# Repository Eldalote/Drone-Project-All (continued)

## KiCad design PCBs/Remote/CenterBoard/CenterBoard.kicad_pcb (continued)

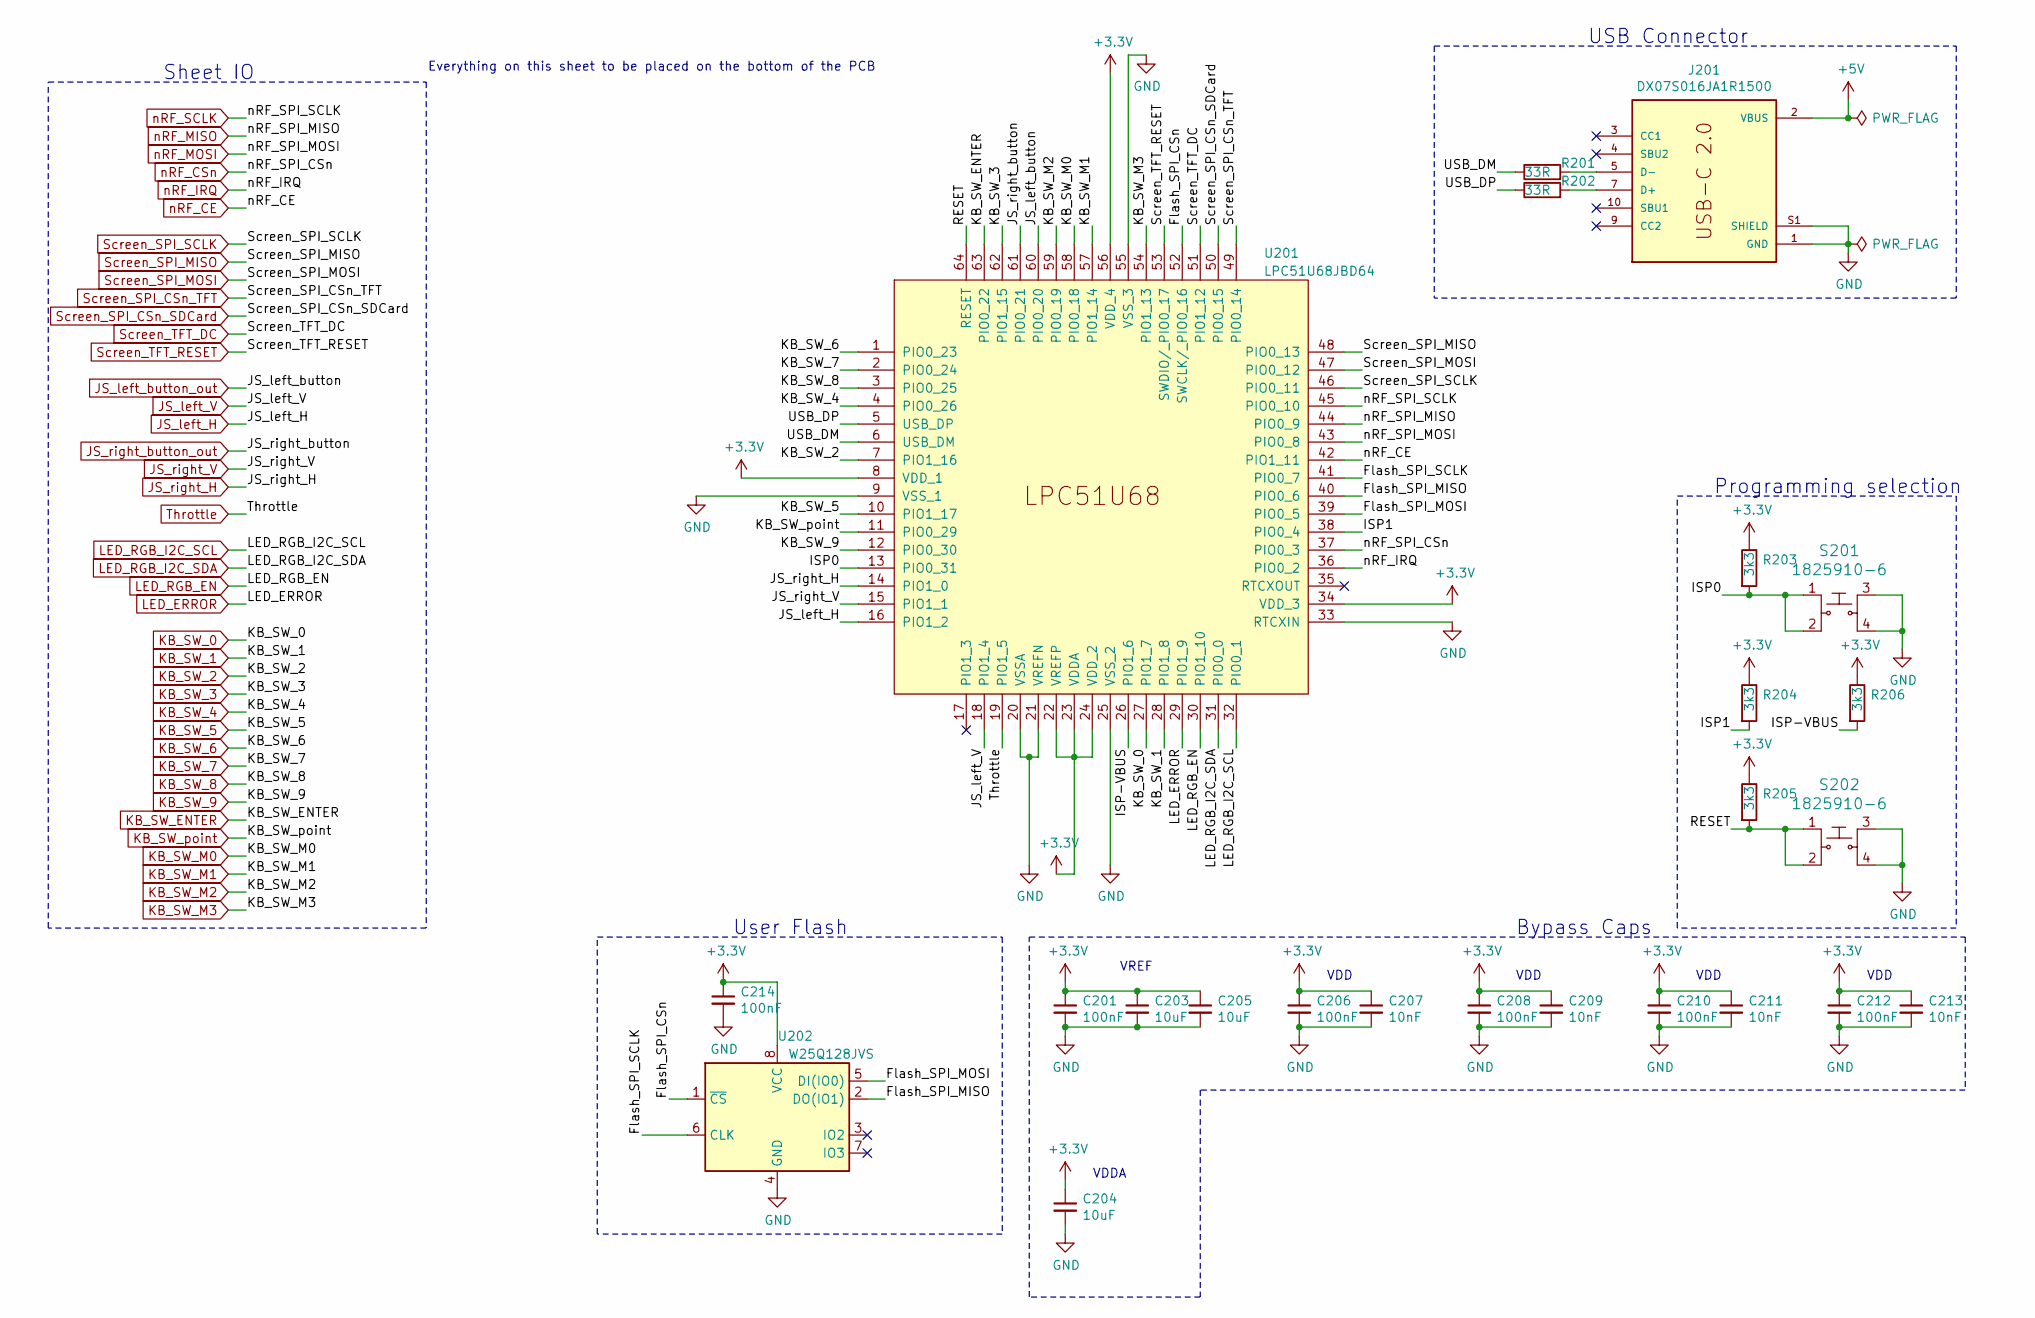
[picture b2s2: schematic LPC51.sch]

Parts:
C201, C206, C208, C210, C212, C214: 100nF; C_0402_1005Metric; LCSC C1525
C203, C204, C205: 10uF; C_0402_1005Metric; LCSC C15525
C207, C209, C211, C213: 10nF; C_0402_1005Metric; LCSC C15195
J201: DX07S016JA1R1500; JAE_DX07S016JA1R1500; DigiKey 670-DX07S016JA1R1500CT-ND
R201, R202: 33R; R_0603_1608Metric_Pad1.05x0.95mm_HandSolder; DigiKey P123790CT-ND
R203, R204, R205, R206: 3k3; R_0603_1608Metric_Pad1.05x0.95mm_HandSolder; LCSC C22978
S201, S202: 1825910-6; Switch_Tactile_THT_6x6mm; DigiKey 450-1650-ND
U201: LPC51U68JBD64; LQFP-64_10x10mm_P0.5mm; DigiKey 568-13909-ND
U202: W25Q128JVS; SOIC-8_5.23x5.23mm_P1.27mm; LCSC C97521

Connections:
+5V: J201.2 (VBUS), J201.11 (VBUS); also elsewhere on the board
/LPC51/Flash_SPI_CSn: U201.52 (SWCLK/_PIO0_16), U202.1 (~CS)
/LPC51/Flash_SPI_MISO: U201.40 (PIO0_6), U202.2 (DO(IO1))
/LPC51/Flash_SPI_MOSI: U201.39 (PIO0_5), U202.5 (DI(IO0))
/LPC51/Flash_SPI_SCLK: U201.41 (PIO0_7), U202.6 (CLK)
/LPC51/ISP0: R203.2, S201.1, S201.2, U201.13 (PIO0_31)
/LPC51/ISP1: R204.2, U201.38 (PIO0_4)
/LPC51/ISP-VBUS: R206.2, U201.26 (PIO1_6)
/LPC51/RESET: R205.2, S202.1, S202.2, U201.64 (RESET)
/LPC51/USB_DM: R201.1, U201.6 (USB_DM)
/LPC51/USB_DP: R202.1, U201.5 (USB_DP)
GND: C201.2, C203.2, C204.2, C205.2, C206.2, C207.2, C208.2, C209.2, C210.2, C211.2, C212.2, C213.2, C214.2, J201.1 (GND), J201.12 (GND), J201.S1 (SHIELD), J201.S2 (SHIELD), J201.S3 (SHIELD), J201.S4 (SHIELD), J201.S5 (SHIELD), J201.S6 (SHIELD), S201.3, S201.4, S202.3, S202.4, U201.9 (VSS_1), U201.20 (VSSA), U201.21 (VREFN), U201.25 (VSS_2), U201.33 (RTCXIN), U201.55 (VSS_3), U202.4 (GND); also elsewhere on the board
JS_left_H: U201.16 (PIO1_2); also elsewhere on the board
JS_left_V: U201.18 (PIO1_4); also elsewhere on the board
JS_left_button_out: U201.60 (PIO0_20); also elsewhere on the board
JS_right_H: U201.14 (PIO1_0); also elsewhere on the board
JS_right_V: U201.15 (PIO1_1); also elsewhere on the board
JS_right_button_out: U201.61 (PIO0_21); also elsewhere on the board
KB_SW_0: U201.27 (PIO1_7); also elsewhere on the board
KB_SW_1: U201.28 (PIO1_8); also elsewhere on the board
KB_SW_2: U201.7 (PIO1_16); also elsewhere on the board
KB_SW_3: U201.62 (PIO1_15); also elsewhere on the board
KB_SW_4: U201.4 (PIO0_26); also elsewhere on the board
KB_SW_5: U201.10 (PIO1_17); also elsewhere on the board
KB_SW_6: U201.1 (PIO0_23); also elsewhere on the board
KB_SW_7: U201.2 (PIO0_24); also elsewhere on the board
KB_SW_8: U201.3 (PIO0_25); also elsewhere on the board
KB_SW_9: U201.12 (PIO0_30); also elsewhere on the board
KB_SW_ENTER: U201.63 (PIO0_22); also elsewhere on the board
KB_SW_M0: U201.58 (PIO0_18); also elsewhere on the board
KB_SW_M1: U201.57 (PIO1_14); also elsewhere on the board
KB_SW_M2: U201.59 (PIO0_19); also elsewhere on the board
KB_SW_M3: U201.54 (PIO1_13); also elsewhere on the board
KB_SW_point: U201.11 (PIO0_29); also elsewhere on the board
LED_ERROR: U201.29 (PIO1_9); also elsewhere on the board
LED_RGB_EN: U201.30 (PIO1_10); also elsewhere on the board
LED_RGB_I2C_SCL: U201.32 (PIO0_1); also elsewhere on the board
LED_RGB_I2C_SDA: U201.31 (PIO0_0); also elsewhere on the board
unnamed: J201.5 (D-), J201.8 (D-), R201.2
unnamed: J201.6 (D+), J201.7 (D+), R202.2
Screen_SPI_CSn_SDCard: U201.50 (PIO0_15); also elsewhere on the board
Screen_SPI_CSn_TFT: U201.49 (PIO0_14); also elsewhere on the board
Screen_SPI_MISO: U201.48 (PIO0_13); also elsewhere on the board
Screen_SPI_MOSI: U201.47 (PIO0_12); also elsewhere on the board
Screen_SPI_SCLK: U201.46 (PIO0_11); also elsewhere on the board
Screen_TFT_DC: U201.51 (PIO1_12); also elsewhere on the board
Screen_TFT_RESET: U201.53 (SWDIO/_PIO0_17); also elsewhere on the board
Throttle: U201.19 (PIO1_5); also elsewhere on the board
nRF_CE: U201.42 (PIO1_11); also elsewhere on the board
nRF_CSn: U201.37 (PIO0_3); also elsewhere on the board
nRF_IRQ: U201.36 (PIO0_2); also elsewhere on the board
nRF_MISO: U201.44 (PIO0_9); also elsewhere on the board
nRF_MOSI: U201.43 (PIO0_8); also elsewhere on the board
nRF_SCLK: U201.45 (PIO0_10); also elsewhere on the board

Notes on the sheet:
Bypass Caps
VREF
VDDA
VDD
Programming selection
USB Connector
User Flash
Sheet IO
Everything on this sheet to be placed on the bottom of the PCB

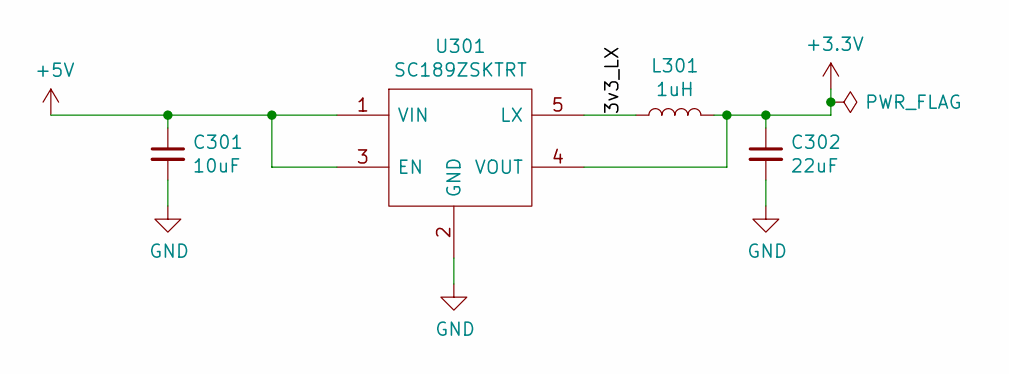
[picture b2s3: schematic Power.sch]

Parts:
C301: 10uF; C_0805_2012Metric; LCSC C15850
C302: 22uF; C_0805_2012Metric; LCSC C45783
L301: 1uH; L_3012_TDK; Mouser 810-VLS3012CX-1R0M-1
U301: SC189ZSKTRT; SOT95P280X145-5N; Mouser Part Number 947-SC189ZSKTRT

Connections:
+5V: C301.1, U301.1 (VIN), U301.3 (EN); also elsewhere on the board
/Power/3v3_LX: L301.1, U301.5 (LX)
GND: C301.2, C302.2, U301.2 (GND); also elsewhere on the board

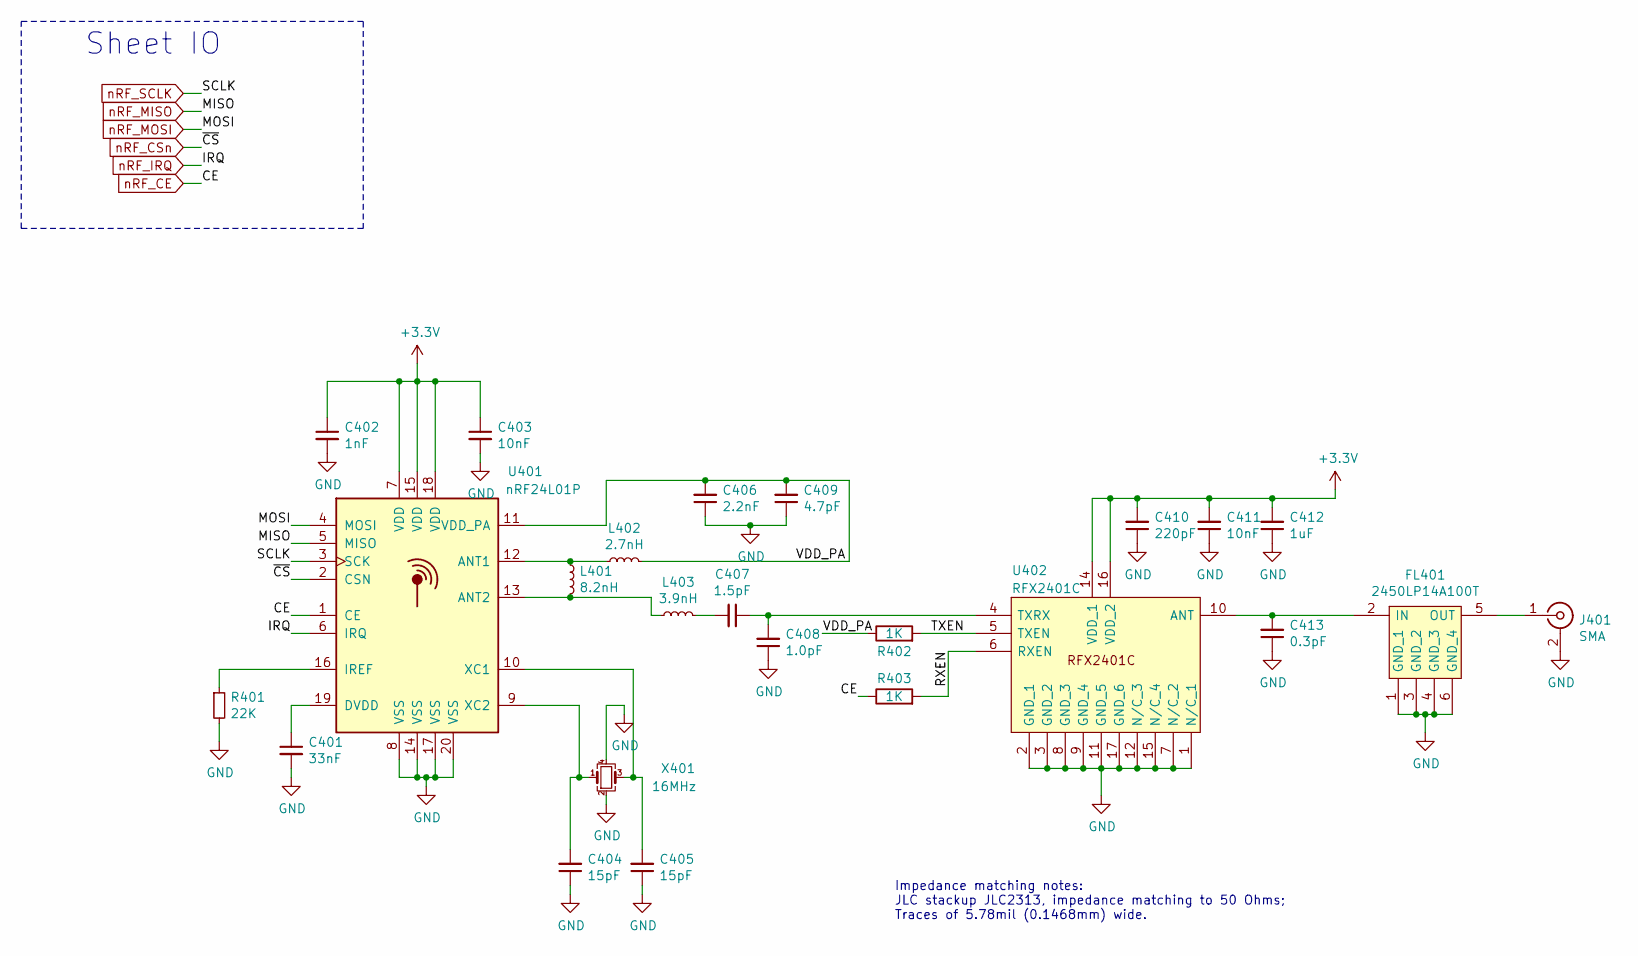
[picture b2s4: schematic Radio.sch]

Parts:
C401: 33nF; C_0603_1608Metric; LCSC C21117
C402: 1nF; C_0402_1005Metric; LCSC C1523
C403, C411: 10nF; C_0402_1005Metric; LCSC C15195
C404, C405: 15pF; C_0402_1005Metric; LCSC C1548
C406: 2.2nF; C_0402_1005Metric; LCSC C1531
C407: 1.5pF; C_0603_1608Metric_Pad1.05x0.95mm_HandSolder; DigiKey 311-1737-1-ND
C408: 1.0pF; C_0603_1608Metric_Pad1.05x0.95mm_HandSolder; DigiKey 1276-1095-1-ND
C409: 4.7pF; C_0402_1005Metric; LCSC C1569
C410: 220pF; C_0402_1005Metric; LCSC C1530
C412: 1uF; C_0402_1005Metric; LCSC C52923
C413: 0.3pF; C_0603_1608Metric_Pad1.05x0.95mm_HandSolder; DigiKey 712-1300-1-ND
FL401: 2450LP14A100T; DigiKey 712-1129-1-ND
J401: SMA; SMA_Samtec_SMA-J-P-X-ST-EM1_EdgeMount; DigiKey CON-SMA-EDGE-S-ND
L401: 8.2nH; L_0402_1005Metric; LCSC C16208
L402: 2.7nH; L_0402_1005Metric; LCSC C27123
L403: 3.9nH; L_0402_1005Metric; LCSC C14033
R401: 22K; R_0402_1005Metric; LCSC C25768
R402, R403: 1K; R_0402_1005Metric; LCSC C11702
U401: nRF24L01P; nRF24L01P-QFN-20-1EP_4x4mm_P0.5mm_EP; DigiKey 1490-1033-1-ND
U402: RFX2401C; QFN-16-1EP_3x3mm_P0.5mm_EP1.75x1.75mm; DigiKey 863-1828-1-ND
X401: 16MHz; Crystal_SMD_3225-4Pin_3.2x2.5mm; LCSC C13738

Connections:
/Radio/RXEN: R403.2, U402.6 (RXEN)
/Radio/TXEN: R402.2, U402.5 (TXEN)
/Radio/VDD_PA: C406.2, C409.2, L402.2, R402.1, U401.11 (VDD_PA)
GND: C401.2, C402.2, C403.2, C404.1, C405.1, C406.1, C408.1, C409.1, C410.1, C411.1, C412.1, C413.1, FL401.1 (GND_1), FL401.3 (GND_2), FL401.4 (GND_3), FL401.6 (GND_4), J401.2 (Ext), R401.2, U401.8 (VSS), U401.14 (VSS), U401.17 (VSS), U401.20 (VSS), U401.21 (EP), U402.1 (N/C_1), U402.2 (GND_1), U402.3 (GND_2), U402.7 (N/C_2), U402.8 (GND_3), U402.9 (GND_4), U402.11 (GND_5), U402.12 (N/C_3), U402.15 (N/C_4), U402.17 (GND_6), X401.2, X401.4; also elsewhere on the board
unnamed: C401.1, U401.19 (DVDD)
unnamed: C404.2, U401.9 (XC2), X401.1
unnamed: C405.2, U401.10 (XC1), X401.3
unnamed: C407.1, C408.2, U402.4 (TXRX)
unnamed: C407.2, L403.2
unnamed: C413.2, FL401.2 (IN), U402.10 (ANT)
unnamed: FL401.5 (OUT), J401.1 (In)
unnamed: L401.1, L402.1, U401.12 (ANT1)
unnamed: L401.2, L403.1, U401.13 (ANT2)
unnamed: R401.1, U401.16 (IREF)
nRF_CE: R403.1, U401.1 (CE); also elsewhere on the board
nRF_CSn: U401.2 (CSN); also elsewhere on the board
nRF_IRQ: U401.6 (IRQ); also elsewhere on the board
nRF_MISO: U401.5 (MISO); also elsewhere on the board
nRF_MOSI: U401.4 (MOSI); also elsewhere on the board
nRF_SCLK: U401.3 (SCK); also elsewhere on the board

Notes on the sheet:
Sheet IO
Impedance matching notes: JLC stackup JLC2313, impedance matching to 50 Ohms; Traces of 5.78mil (0.1468mm) wide.

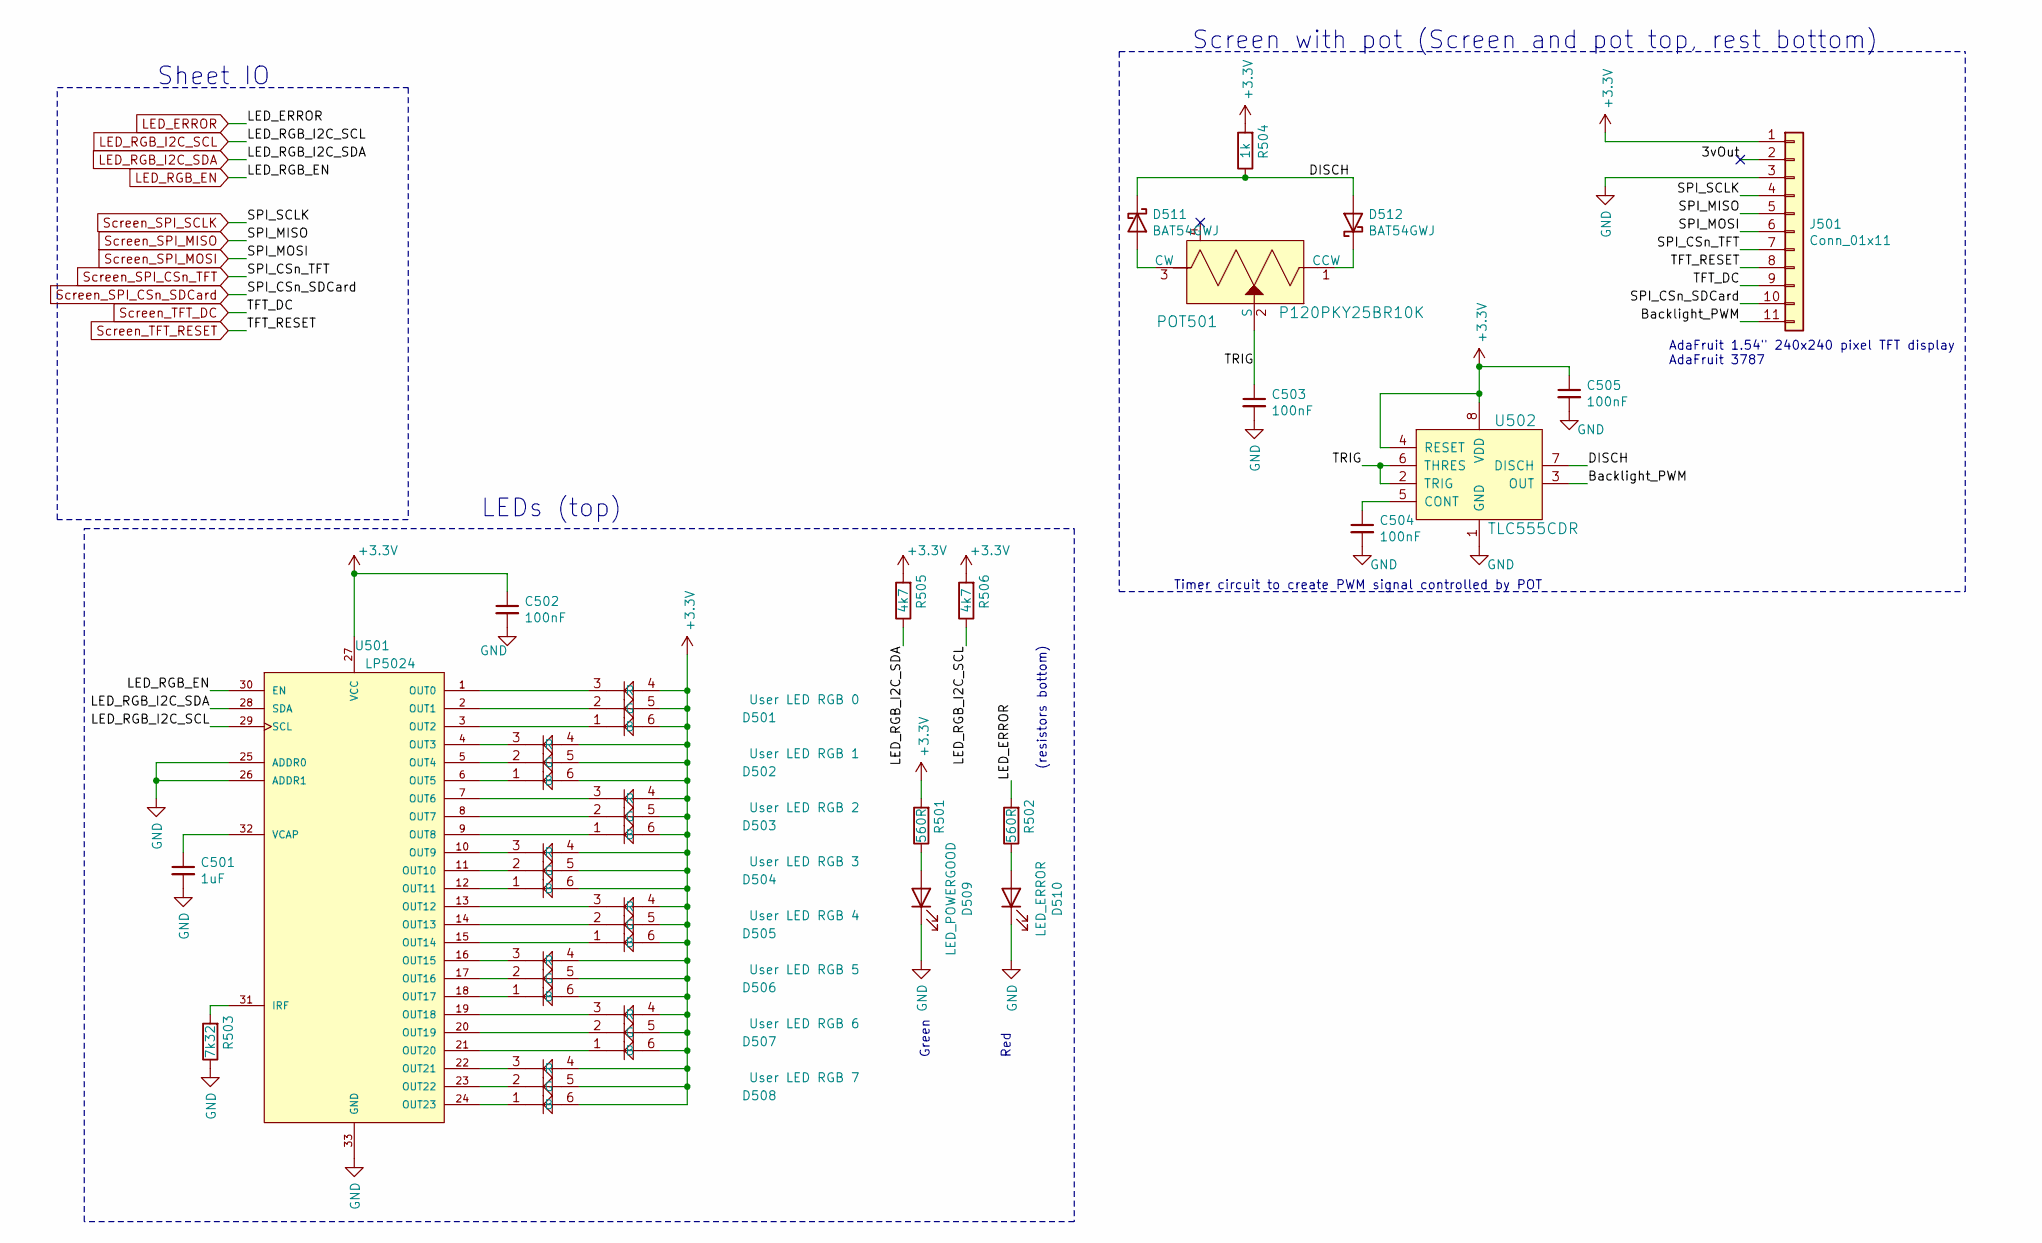
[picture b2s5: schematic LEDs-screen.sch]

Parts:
C501: 1uF; C_0805_2012Metric_Pad1.15x1.40mm_HandSolder; LCSC C28323
C502: 100nF; C_0805_2012Metric_Pad1.15x1.40mm_HandSolder; LCSC C49678
C503, C504, C505: 100nF; C_0402_1005Metric; LCSC C1525
D501: User LED RGB 0; LED_RGB_PLCC-6
D502: User LED RGB 1; LED_RGB_PLCC-6
D503: User LED RGB 2; LED_RGB_PLCC-6
D504: User LED RGB 3; LED_RGB_PLCC-6
D505: User LED RGB 4; LED_RGB_PLCC-6
D506: User LED RGB 5; LED_RGB_PLCC-6
D507: User LED RGB 6; LED_RGB_PLCC-6
D508: User LED RGB 7; LED_RGB_PLCC-6
D509: LED_POWERGOOD; LED_0805_2012Metric_Pad1.15x1.40mm_HandSolder; DigiKey 475-1410-1-ND
D510: LED_ERROR; LED_0805_2012Metric_Pad1.15x1.40mm_HandSolder; DigiKey 475-1278-1-ND
D511, D512: BAT54GWJ; D_SOD-123; DigiKey 1727-7328-1-ND
J501: Conn_01x11; PinHeader_1x11_P2.54mm_Vertical_SMD_Pin1Left
POT501: P120PKY25BR10K; Potentiometer_P120PK-Y25BR10K; DigiKey 987-1710-ND
R501, R502: 560R; R_0402_1005Metric; LCSC C25796
R503: 7k32; R_0603_1608Metric_Pad1.05x0.95mm_HandSolder; DigiKey 541-7.32KHCT-ND
R504: 1k; R_0402_1005Metric; LCSC C11702
R505, R506: 4k7; R_0402_1005Metric; LCSC C25900
U501: LP5024; QFN-32-1EP_4x4mm_P0.4mm_EP2.9x2.9mm; DigiKey 296-50814-1-ND
U502: TLC555CDR; SOIC-8_W3.9mm; DigiKey 296-1336-1-ND

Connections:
/LEDs and Screen/3vOut: J501.2
/LEDs and Screen/Backlight_PWM: J501.11, U502.3 (OUT)
/LEDs and Screen/DISCH: D511.1 (K), D512.2 (A), R504.1, U502.7 (DISCH)
/LEDs and Screen/TRIG: C503.1, POT501.2 (S), U502.2 (TRIG), U502.6 (THRES)
GND: C501.2, C502.2, C503.2, C504.2, C505.2, D509.1 (K), D510.1 (K), J501.3, R503.1, U501.25 (ADDR0), U501.26 (ADDR1), U501.33 (GND), U502.1 (GND); also elsewhere on the board
LED_ERROR: R502.2; also elsewhere on the board
LED_RGB_EN: U501.30 (EN); also elsewhere on the board
LED_RGB_I2C_SCL: R506.1, U501.29 (SCL); also elsewhere on the board
LED_RGB_I2C_SDA: R505.1, U501.28 (SDA); also elsewhere on the board
unnamed: C501.1, U501.32 (VCAP)
unnamed: C504.1, U502.5 (CONT)
unnamed: D501.1, U501.3 (OUT2)
unnamed: D501.2, U501.2 (OUT1)
unnamed: D501.3, U501.1 (OUT0)
unnamed: D502.1, U501.6 (OUT5)
unnamed: D502.2, U501.5 (OUT4)
unnamed: D502.3, U501.4 (OUT3)
unnamed: D503.1, U501.9 (OUT8)
unnamed: D503.2, U501.8 (OUT7)
unnamed: D503.3, U501.7 (OUT6)
unnamed: D504.1, U501.12 (OUT11)
unnamed: D504.2, U501.11 (OUT10)
unnamed: D504.3, U501.10 (OUT9)
unnamed: D505.1, U501.15 (OUT14)
unnamed: D505.2, U501.14 (OUT13)
unnamed: D505.3, U501.13 (OUT12)
unnamed: D506.1, U501.18 (OUT17)
unnamed: D506.2, U501.17 (OUT16)
unnamed: D506.3, U501.16 (OUT15)
unnamed: D507.1, U501.21 (OUT20)
unnamed: D507.2, U501.20 (OUT19)
unnamed: D507.3, U501.19 (OUT18)
unnamed: D508.1, U501.24 (OUT23)
unnamed: D508.2, U501.23 (OUT22)
unnamed: D508.3, U501.22 (OUT21)
unnamed: D509.2 (A), R501.1
unnamed: D510.2 (A), R502.1
unnamed: D511.2 (A), POT501.3 (CW)
unnamed: D512.1 (K), POT501.1 (CCW)
unnamed: R503.2, U501.31 (IRF)
Screen_SPI_CSn_SDCard: J501.10; also elsewhere on the board
Screen_SPI_CSn_TFT: J501.7; also elsewhere on the board
Screen_SPI_MISO: J501.5; also elsewhere on the board
Screen_SPI_MOSI: J501.6; also elsewhere on the board
Screen_SPI_SCLK: J501.4; also elsewhere on the board
Screen_TFT_DC: J501.9; also elsewhere on the board
Screen_TFT_RESET: J501.8; also elsewhere on the board

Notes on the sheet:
AdaFruit 1.54" 240x240 pixel TFT display AdaFruit 3787
Green
Red
Sheet IO
Screen with pot (Screen and pot top, rest bottom)
LEDs (top)
Timer circuit to create PWM signal controlled by POT
(resistors bottom)

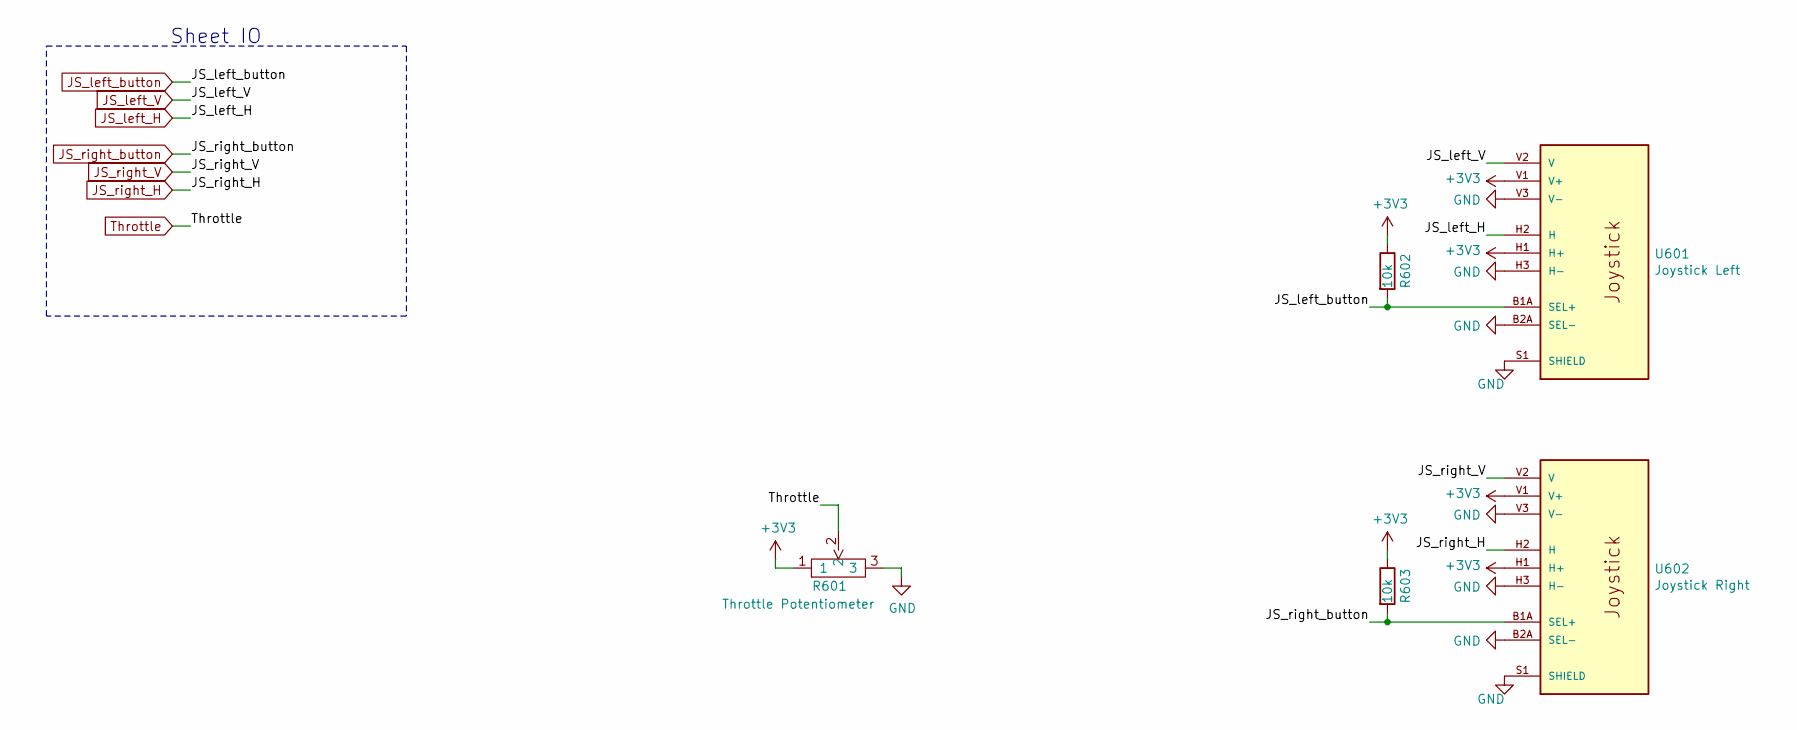
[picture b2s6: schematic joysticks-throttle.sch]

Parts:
R601: Throttle Potentiometer; PTA6043; DigiKey PTA6043-2015DPB103-ND
R602, R603: 10k; R_0805_2012Metric_Pad1.15x1.40mm_HandSolder; LCSC C17414
U601: Joystick Left; Sparkfun_COM-09032; DigiKey 1568-1526-ND
U602: Joystick Right; Sparkfun_COM-09032; DigiKey 1568-1526-ND

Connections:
GND: R601.3, U601.B2A (SEL-), U601.H3 (H-), U601.S1 (SHIELD), U601.S2 (SHIELD), U601.S3 (SHIELD), U601.S4 (SHIELD), U601.V3 (V-), U602.B2A (SEL-), U602.H3 (H-), U602.S1 (SHIELD), U602.S2 (SHIELD), U602.S3 (SHIELD), U602.S4 (SHIELD), U602.V3 (V-); also elsewhere on the board
JS_left_H: U601.H2 (H); also elsewhere on the board
JS_left_V: U601.V2 (V); also elsewhere on the board
JS_left_button: R602.2, U601.B1A (SEL+); also elsewhere on the board
JS_right_H: U602.H2 (H); also elsewhere on the board
JS_right_V: U602.V2 (V); also elsewhere on the board
JS_right_button: R603.2, U602.B1A (SEL+); also elsewhere on the board
Throttle: R601.2; also elsewhere on the board

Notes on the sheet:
Sheet IO

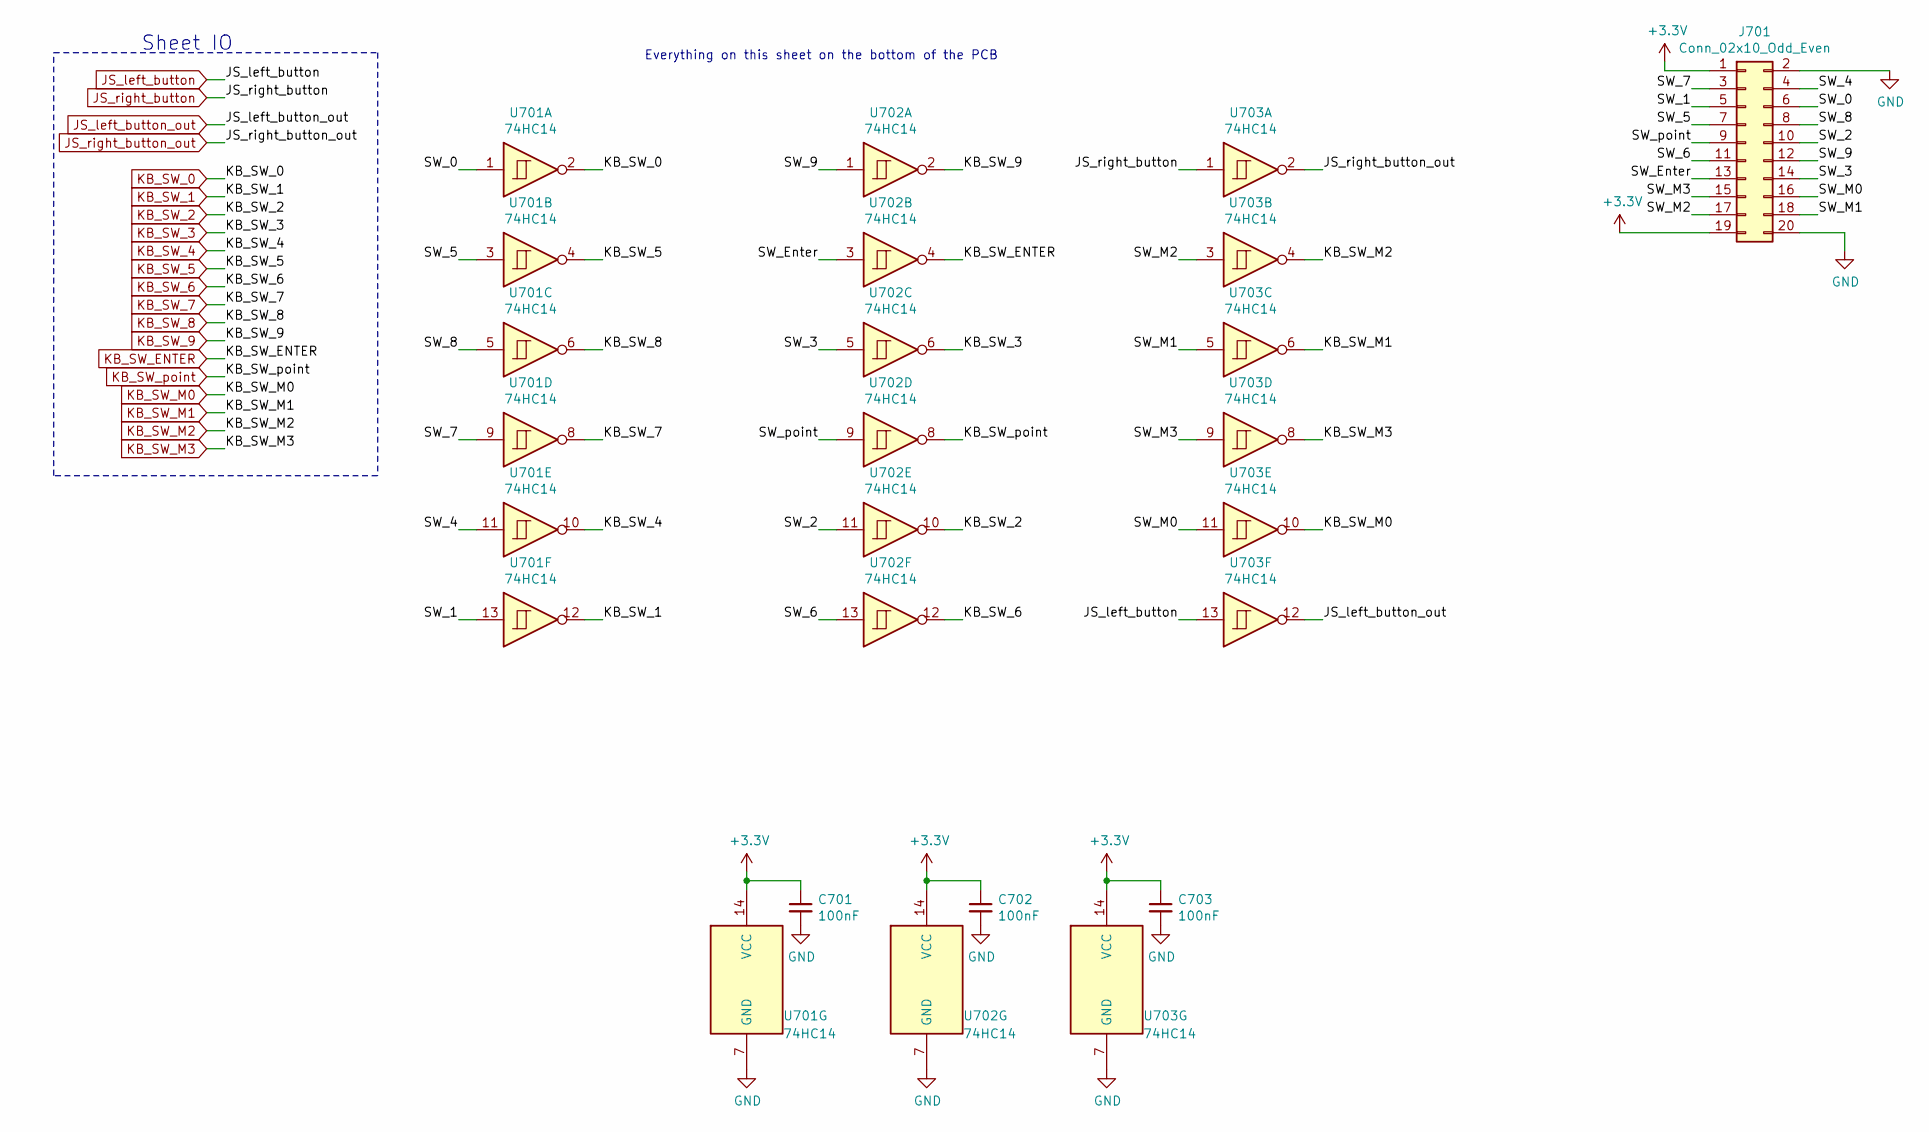
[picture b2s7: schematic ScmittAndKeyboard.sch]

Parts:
C701, C702, C703: 100nF; C_0402_1005Metric; LCSC C1525
J701: Conn_02x10_Odd_Even; PinHeader_2x10_P2.54mm_Vertical
U701, U702, U703: 74HC14; SOIC-14_3.9x8.7mm_P1.27mm

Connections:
/Keyboard connector and Schmitt triggers/SW_0: J701.6, U701.1
/Keyboard connector and Schmitt triggers/SW_1: J701.5, U701.13
/Keyboard connector and Schmitt triggers/SW_2: J701.10, U702.11
/Keyboard connector and Schmitt triggers/SW_3: J701.14, U702.5
/Keyboard connector and Schmitt triggers/SW_4: J701.4, U701.11
/Keyboard connector and Schmitt triggers/SW_5: J701.7, U701.3
/Keyboard connector and Schmitt triggers/SW_6: J701.11, U702.13
/Keyboard connector and Schmitt triggers/SW_7: J701.3, U701.9
/Keyboard connector and Schmitt triggers/SW_8: J701.8, U701.5
/Keyboard connector and Schmitt triggers/SW_9: J701.12, U702.1
/Keyboard connector and Schmitt triggers/SW_Enter: J701.13, U702.3
/Keyboard connector and Schmitt triggers/SW_M0: J701.16, U703.11
/Keyboard connector and Schmitt triggers/SW_M1: J701.18, U703.5
/Keyboard connector and Schmitt triggers/SW_M2: J701.17, U703.3
/Keyboard connector and Schmitt triggers/SW_M3: J701.15, U703.9
/Keyboard connector and Schmitt triggers/SW_point: J701.9, U702.9
GND: C701.2, C702.2, C703.2, J701.2, J701.20, U701.7 (GND), U702.7 (GND), U703.7 (GND); also elsewhere on the board
JS_left_button: U703.13; also elsewhere on the board
JS_left_button_out: U703.12; also elsewhere on the board
JS_right_button: U703.1; also elsewhere on the board
JS_right_button_out: U703.2; also elsewhere on the board
KB_SW_0: U701.2; also elsewhere on the board
KB_SW_1: U701.12; also elsewhere on the board
KB_SW_2: U702.10; also elsewhere on the board
KB_SW_3: U702.6; also elsewhere on the board
KB_SW_4: U701.10; also elsewhere on the board
KB_SW_5: U701.4; also elsewhere on the board
KB_SW_6: U702.12; also elsewhere on the board
KB_SW_7: U701.8; also elsewhere on the board
KB_SW_8: U701.6; also elsewhere on the board
KB_SW_9: U702.2; also elsewhere on the board
KB_SW_ENTER: U702.4; also elsewhere on the board
KB_SW_M0: U703.10; also elsewhere on the board
KB_SW_M1: U703.6; also elsewhere on the board
KB_SW_M2: U703.4; also elsewhere on the board
KB_SW_M3: U703.8; also elsewhere on the board
KB_SW_point: U702.8; also elsewhere on the board

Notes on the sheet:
Sheet IO
Everything on this sheet on the bottom of the PCB

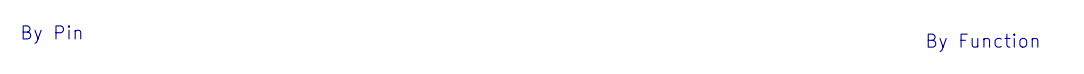
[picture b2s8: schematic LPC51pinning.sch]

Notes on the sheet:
By Pin
By Function

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
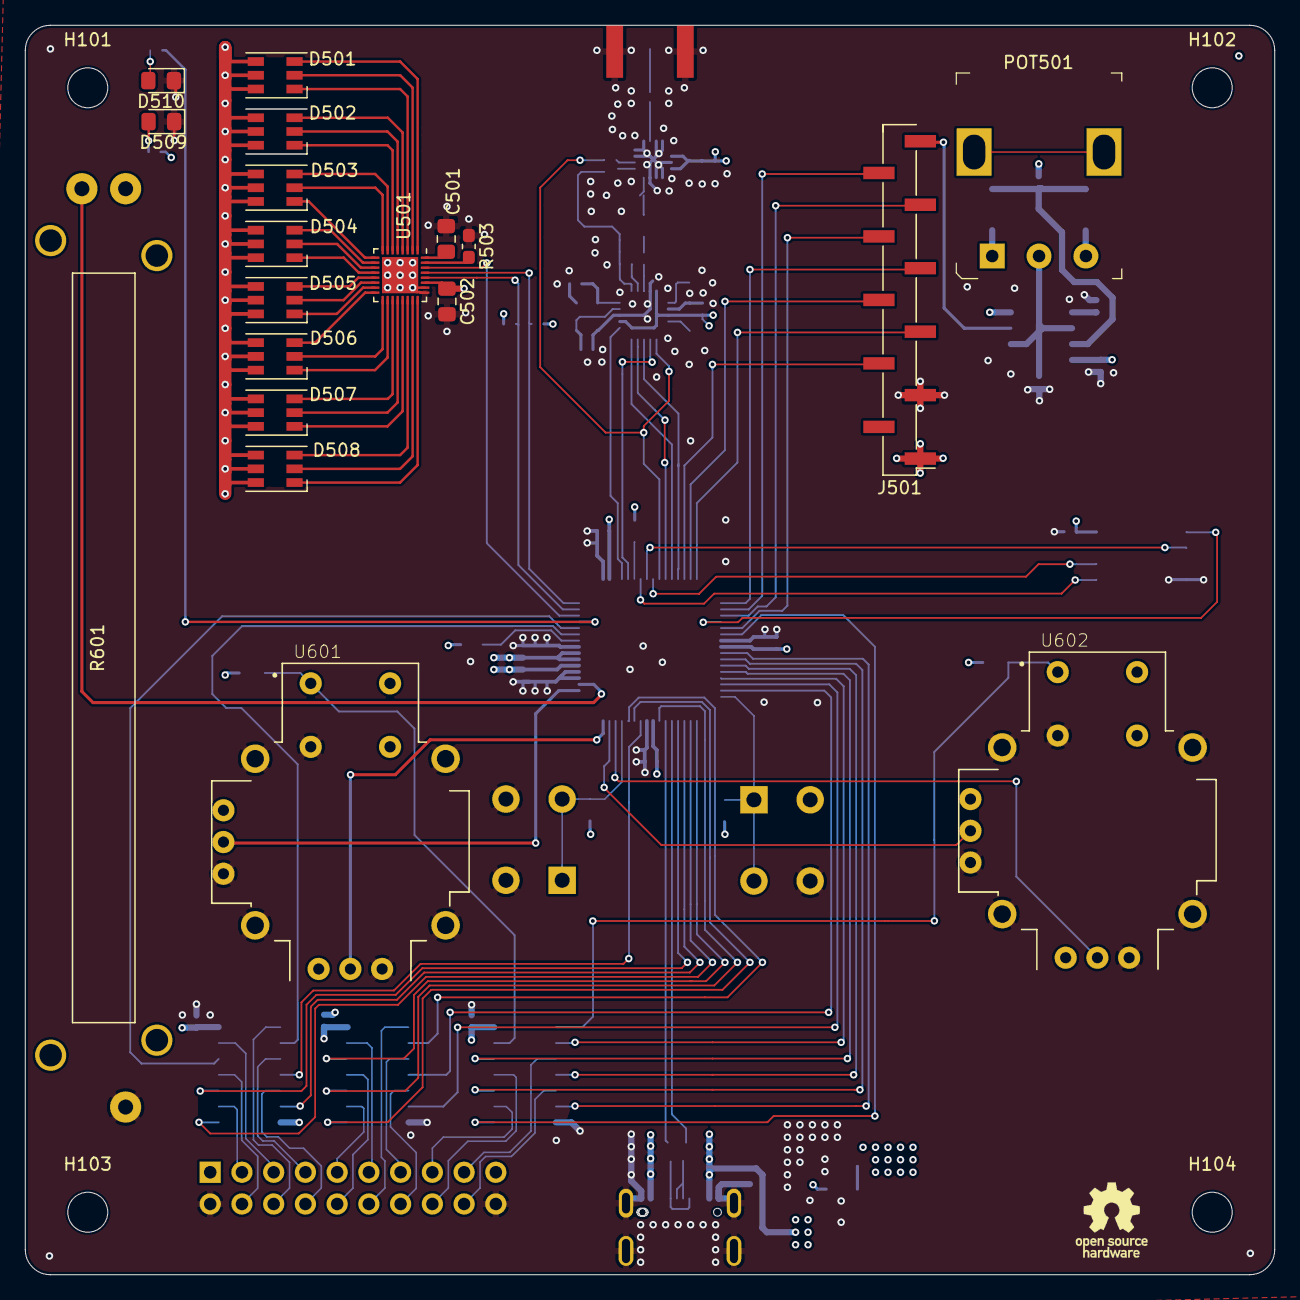
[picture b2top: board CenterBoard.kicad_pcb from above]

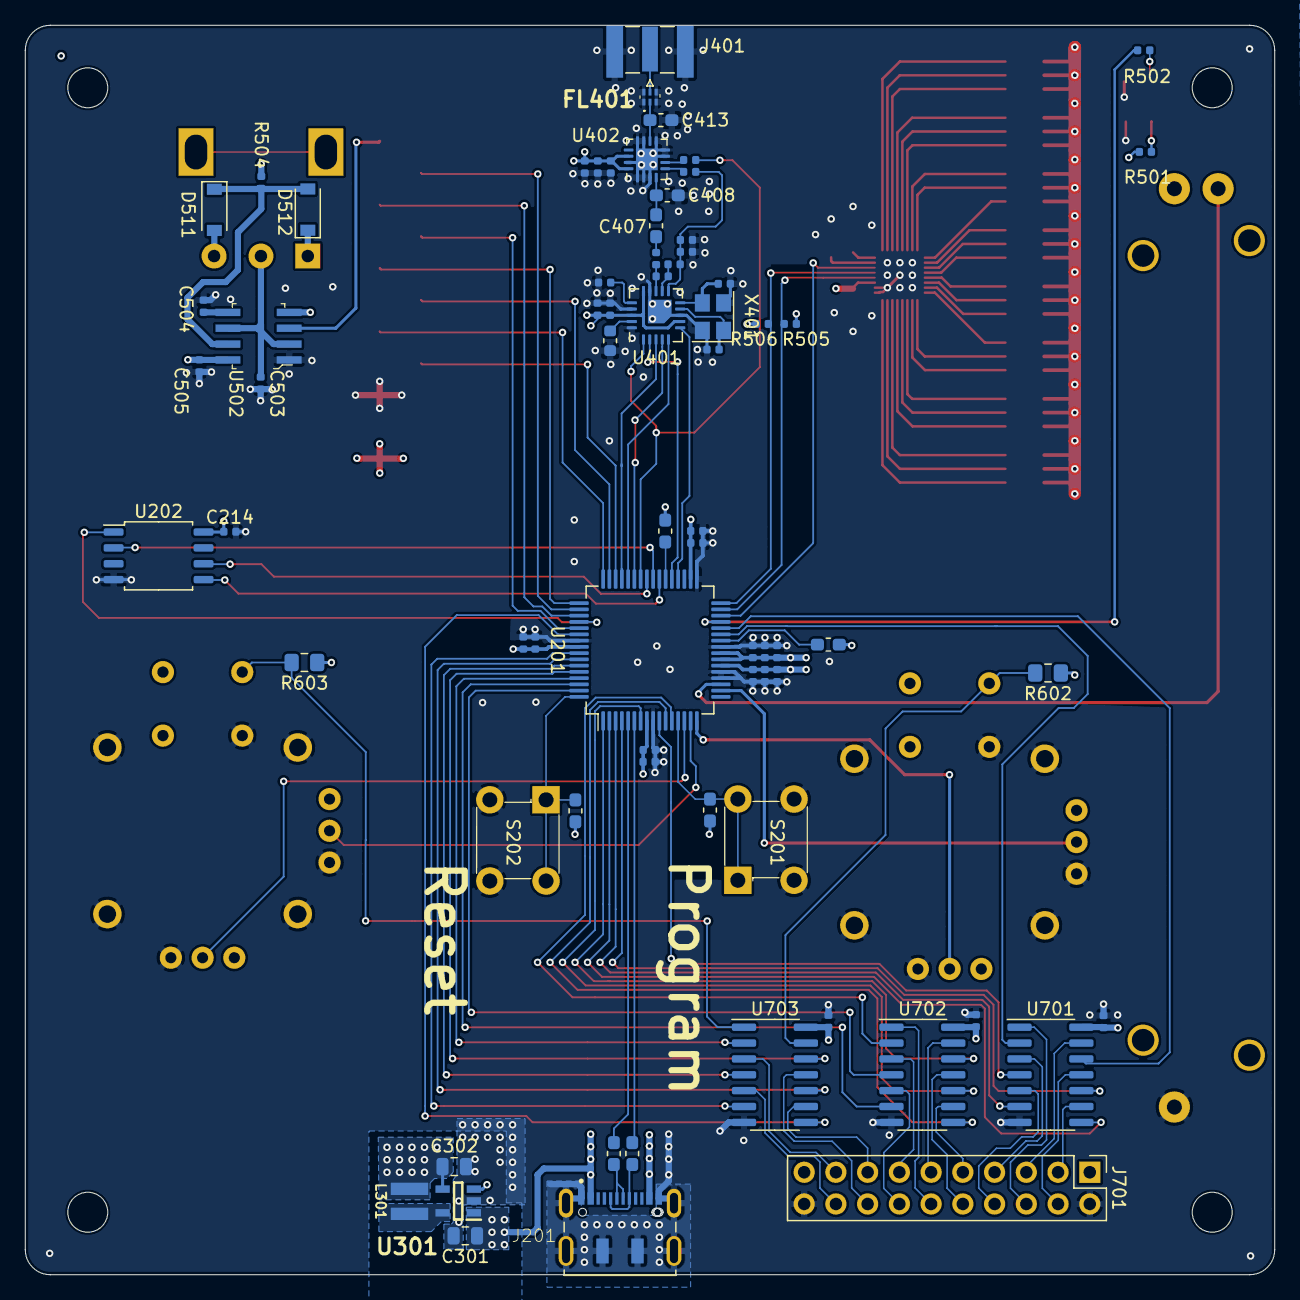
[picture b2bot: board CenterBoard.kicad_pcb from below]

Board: 4 copper layers, 100.0 x 100.0 mm, 96 parts (72 on the bottom side), 121 nets.
